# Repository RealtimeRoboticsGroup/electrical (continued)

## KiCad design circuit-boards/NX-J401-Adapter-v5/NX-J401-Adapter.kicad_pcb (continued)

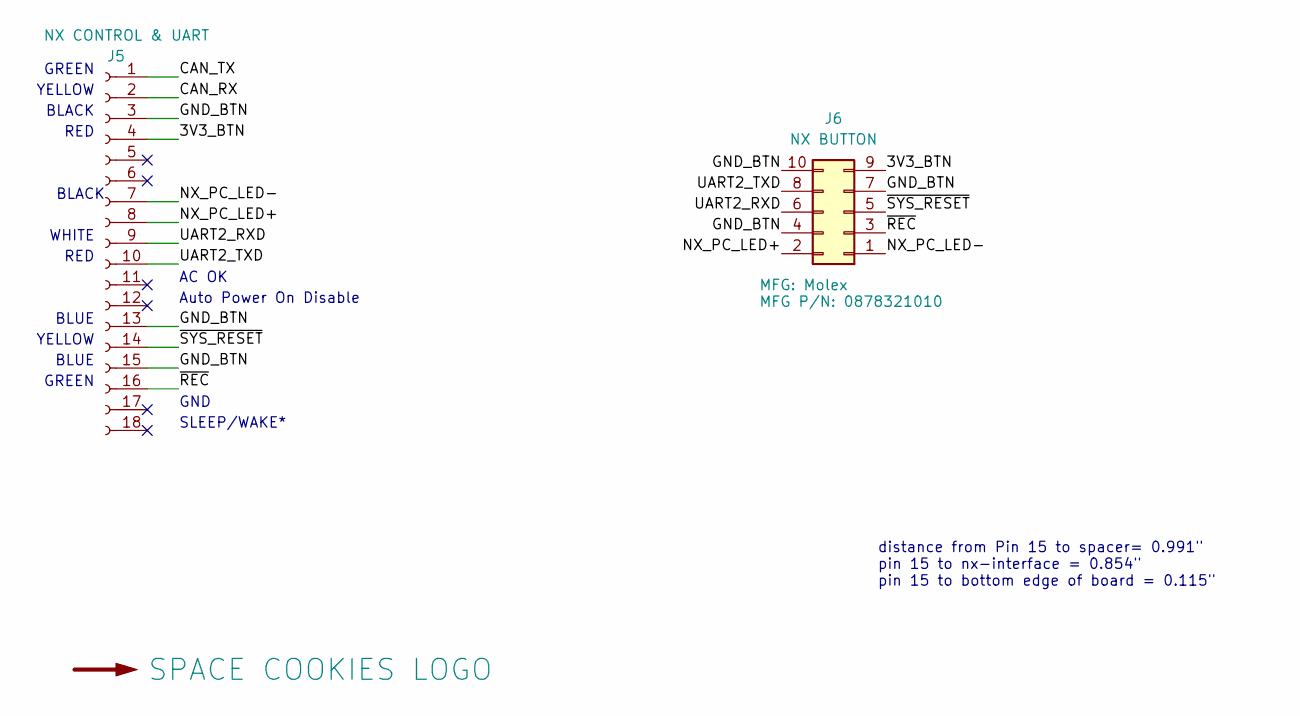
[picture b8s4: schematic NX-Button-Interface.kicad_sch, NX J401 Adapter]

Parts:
J5: NX CONTROL & UART; PinSocket_1x18_P2.54mm_Vertical; MFG P/N PPTC181LFBN-RC
J6: NX BUTTON; Molex-878321010; MFG P/N 0878321010
LOGO2: SPACE COOKIES LOGO; SPACE_COOKIES_LOGO_15mm

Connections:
/NX Button Interface/3V3_BTN: J5.4, J6.9
/NX Button Interface/CAN_RX: J5.2
/NX Button Interface/CAN_TX: J5.1
/NX Button Interface/GND_BTN: J5.3, J5.13, J5.15, J6.4, J6.7, J6.10
/NX Button Interface/NX_PC_LED+: J5.8, J6.2
/NX Button Interface/NX_PC_LED-: J5.7, J6.1
/NX Button Interface/UART2_RXD: J5.9, J6.6
/NX Button Interface/UART2_TXD: J5.10, J6.8
/NX Button Interface/~REC: J5.16, J6.3
/NX Button Interface/~SYS_RESET: J5.14, J6.5

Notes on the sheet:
BLACK
YELLOW
BLUE
RED
AC OK
GND
Auto Power On Disable
SLEEP/WAKE*
GREEN
distance from Pin 15 to spacer= 0.991" pin 15 to nx-interface = 0.854" pin 15 to bottom edge of board = 0.115"
WHITE

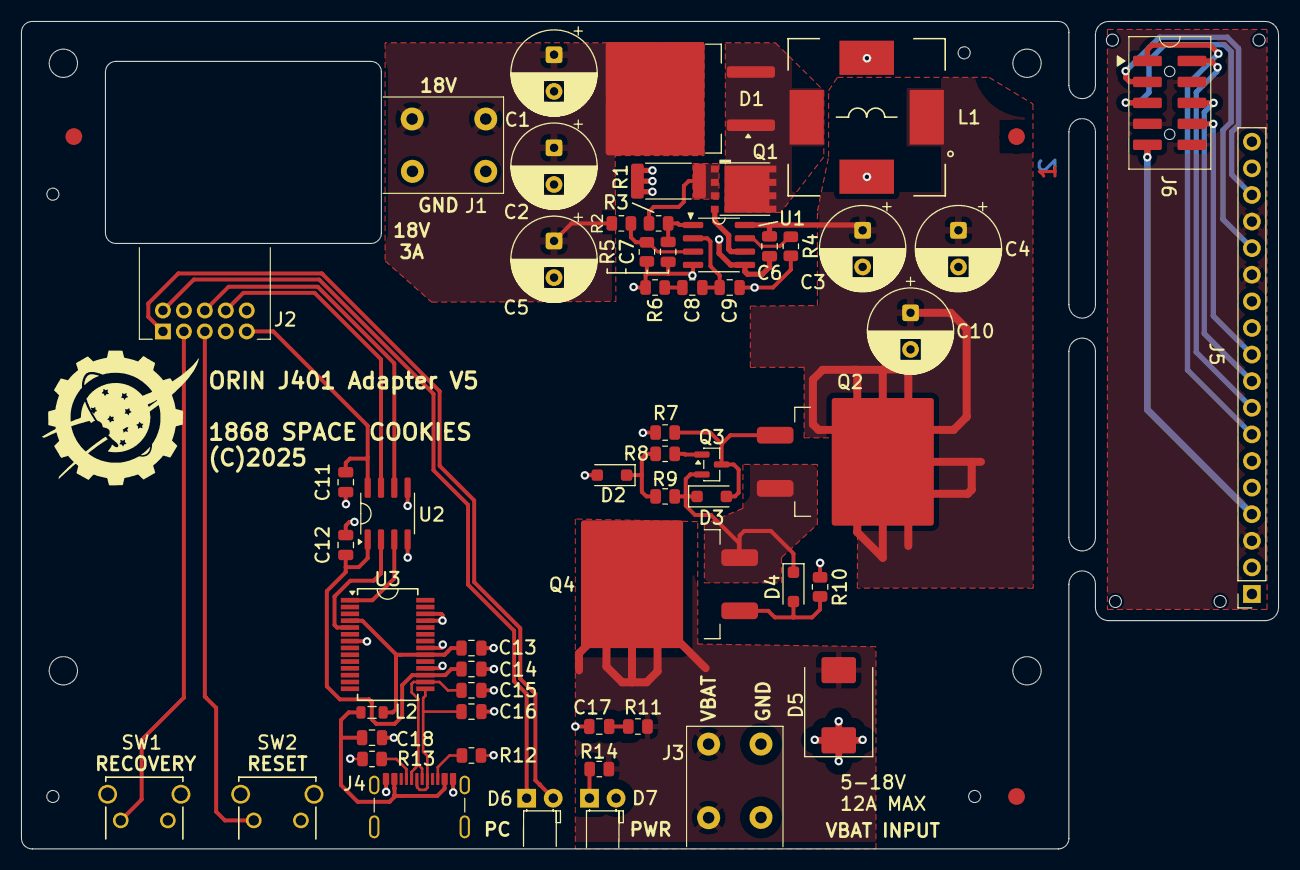
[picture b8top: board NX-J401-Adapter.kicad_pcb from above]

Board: 2 copper layers, 120.0 x 79.0 mm, 73 parts (1 on the bottom side), 45 nets.

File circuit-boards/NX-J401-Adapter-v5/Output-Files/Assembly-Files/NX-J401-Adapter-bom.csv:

"Item","QUANTITY","Reference","Value","MFG","MFG P/N","DIST","DIST P/N"
"1","1","C7","10pF-5%-50V-0805","Samsung Electro-Mechanics","CL21C100CBANNNC","Digikey","1276-2561-1-ND"
"2","1","C13","4.7uF-10%-25V-0805","Samsung Electro-Mechanics","CL21A475KAQNNNE","Digikey","1276-1244-1-ND"
"3","1","C17","4.7uF-10%-50V-0805","Murata Electronics","GRM21BR61H475KE51L","Digikey","490-10751-1-ND"
"4","3","C1,C2,C5","56uF 25V","Panasonic Electronic Components","25SEPF56M","Mouser","667-25SEPF56M "
"5","3","C11,C12,C14","0.1uF-10%-25V-0805","KEMET","C0805C104K3RACTU","Digikey","399-C0805C104K3RACTUCT-ND"
"6","2","C15,C16","47pF-5%-50V-0805","YAGEO","CC0805JRNPO9BN470","Digikey","311-1107-1-ND"
"7","3","C3,C4,C10","120uF 25V","Panasonic","25SEK120M","Digikey","P122635-ND"
"8","2","C6,C8","0.22uF-10%-50V-0805","KEMET","C0805C224K5RAC7800","Digikey","399-C0805C224K5RACTUCT-ND"
"9","2","C9,C18","0.01uF-10%-50V-0805","Samsung Electro-Mechanics","CL21B103KBANNNC","Digikey","1276-1015-1-ND"
"10","1","D1","STPS20M100SG-TR","STmicroelectronics","STPS20M100SG-TR","Digikey","497-10993-1-ND"
"11","1","D2","20V","Nexperia","BZT52H-C20,115","Digikey","1727-3596-1-ND"
"12","1","D5","24V","Littelfuse","SMDJ24CA","Digikey","SMDJ24CACT-ND"
"13","2","D3,D4","15V","Nexperia","BZT52H-C15,115","Digikey","1727-3593-1-ND"
"14","2","D6,D7","PC,PWR","Kingbright","WP937EGW","Digikey","754-1751-ND"
"15","1","J2","NX BUTTON","Molex","0878321010","Digikey","WM4227-ND"
"16","1","J4","USB_C_Receptacle_USB2.0_14P","Molex","2171790001","Digikey","900-2171790001CT-ND"
"17","2","J1,J3","Power,V_OUT","Weidmuller","1824740000","Digikey","281-2110-ND"
"18","1","L1","4.7 uH-8m-20%","Vishay Dale","IHLE5050FHER4R7M5A ","Mouser","70-IHLE5050FHR4R7M5A "
"19","1","L2","HZ0805E601R-10","Laird-Signal Integrity Products","HZ0805E601R-10","Digikey","240-2399-1-ND"
"20","1","Q1","CSD16322Q5","Texas Instruments","CSD16322Q5","Digikey","296-25112-1-ND"
"21","1","Q3","MMBT3906LT1G","onsemi","MMBT3906LT1G","Digikey","MMBT3906LT1GOSCT-ND"
"22","2","Q2,Q4","SQM40061EL_GE3","Vishay Siliconix","SQM40061EL_GE3","Digikey","SQM40061EL_GE3CT-ND"
"23","1","R1","4.0m-1%-2512","Bourns Inc.","CRE2512-FZ-R004E-3","Digikey","CRE2512-FZ-R004E-3CT-ND"
"24","1","R2","14.0k-1%-0805","Yageo","RC0805FR-0714KL","Digikey","311-14.0KCRCT-ND"
"25","1","R3","100R-1%-0805","Yageo","RC0805FR-07100RL","Digikey","311-100CRCT-ND"
"26","1","R4","59.0k-1%-0805","Yageo","RC0805FR-0759KL","Digikey","311-59.0KCRCT-ND"
"27","1","R11","1.00R-1%-0805","Vishay Dale","CRCW08051R00FKEAHP","Digikey","541-1.00TCT-ND"
"28","3","R5,R6,R9","1.05k-1%-0805","Yageo","RC0805FR-071K05L","Digikey","311-1.05KCRCT-ND"
"29","6","R7,R8,R10,R12-R14","5.10k-1%-0805","Yageo","RC0805FR-075K1L","Digikey","311-5.10KCRCT-ND"
"30","2","SW1,SW2","RECOVERY,RESET","E-Switch","TL1105VF100Q","Digikey","EG2507-ND"
"31","1","U1","LM3478MA","Texas Instruments","LM3478MAX/NOPB","Digikey","296-38111-1-ND"
"32","1","U2","ISO6721BDR","Texas Instruments","ISO6721BDR","Digikey","296-ISO6721BDRCT-ND"
"33","1","U3","FT232RNL","FTDI","FT232RNL","Digikey","768-FT232RNL-REELCT-ND"

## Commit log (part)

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2025-01-05 Initial commit from private repo
2025-01-14 Initial Checkin of NX J401 Adapter PCB
2025-01-14 Update NX J401 Adapter to add PC LED and swap buttons
2025-01-14 Add NX Button Interface Board
2025-01-16 Update NX-J401 and NX Button Interface boards
2025-01-16 Clarify schematic analog ground
2025-01-16 Minor fixes
2025-04-26 Add NX Indicator board. Change to one oscillator
2025-04-28 Initial checkin of WIP
2025-04-28 Changed to 1 encoder, all connectors to SMD right angle SL
2025-06-08 Add Pico CAN PCBA
2025-06-08 Minor update to PicoCAN. Add JLC assembly docs
2025-06-10 Checkin post review
2025-06-14 Changed oscillator back to ECS5032
2025-06-14 Missed schematic
2025-06-14 Update BOM
2025-06-25 Copy of https://github.com/Pier836/MCP2518FD-on-Raspberry-Pico to start picocan
2025-06-25 Set defs to match picoCAN board. Tweak code to compile
2025-09-17 Initial checkin of Button Interface and Adapter with USB-serial adapter addition
2025-09-20 Initial check in of Mini PDB V2
2025-09-20 Changed drawing sheet to Space Cookies
2025-09-20 Update using Space Cookies sheet template
2025-09-26 adjust header to match nx-adapter
2025-09-28 Add over voltage protection to NX adapter circuit. Also reduce component height
2025-10-07 Fix name on PCB
2025-10-19 Change NX-J401-Adapter to reduce the PCB standoff spacing.
2025-10-19 Update NX-ButtonInterface-v2 to be compatible with NX-J401-Adapter-v5
2025-10-19 Update step file of NX-J401-Adapter
2025-10-23 Update silk to new part number
2025-10-23 Update NX J401 to combine button interface and adapter. change header to right angle
2025-10-25 Fix bom to reduce line items. Addd zip tie slots. Add 1.5mm tooling holes
2025-11-09 Add ability to build pico2 binaries with bazel
2025-11-09 Add license
2025-11-12 Add bazel target for picocan and binary for it
2025-11-12 Fix usb printing
2025-11-25 Add ribbon cable connector and cable to schematic
2025-12-13 Adding ibom for J401 Adapter board
2025-12-18 Fixed IDC connector part number
2025-12-26 Initial check in
2025-12-26 Update footprints
2025-12-27 Pico Button Board initial placement
2025-12-28 Pico Button Board initial pcb checkin
2025-12-28 Update Pico Button Board Layout
2025-12-28 Updated Pico2 step file
2025-12-30 Changed button input circuit to use mux. Changed ADC3 to an external SPI ADC
2025-12-30 Minor schematic fix
2025-12-31 Add power over CAN to supply joystick from button interfaces.
2025-12-31 Change diodes to schottky. Change 5V setpoint to 5.18V
2025-12-31 DNP joystick pull down resistors
2026-01-01 Initial check in of roboRIO interface
2026-01-01 Update HTML bom to for DNPs
2026-01-02 Beam Break initial check in
2026-01-04 Minor schematic field update. Add jupyter notebook for power supply analysis
2026-01-05 Chagned opto-coupler to totem pole output to drive 5V DIO with weak pull-up
2026-01-05 Improved placement and routing
2026-01-06 Increased length to 2.2in
2026-01-21 Added power indicator to button board
2026-01-22 Lower impedance of battery override input
2026-01-25 initial checkin
2026-01-25 modify roborio bom to add sockets to bottom of board
2026-01-25 add bottom silk to gerbers
2026-01-25 Update power pour
2026-01-25 Changed Signal LED to Yellow
2026-02-09 Update RRIB bom to include applicable interfaces
2026-02-22 changed the roborio interface stuffing
2026-02-22 Update roborio interface assy
2026-02-22 Fix inductor mfg part number
2026-03-22 Updated repo license to Solderpad V2.1
2026-03-22 Update Apache License copyright
2026-03-22 Minor update of template to use COPYRIGHT_YEAR instead of YEAR
2026-03-23 Add open source license to mag encoder.
2026-05-18 Changed canable to use 3.3V power form USB to use key-e connector that breaks out USB and 3V3
2026-05-19 WIP update
2026-05-20 Changed USB header ot pico lock and light pipe to single row
2026-05-21 Added ideal diode circuit for reverse polarity and output or-ing
2026-05-22 Starting component placement
2026-05-22 rearrange power supply
2026-05-24 Improved placement. Pre-routing
2026-05-24 Initial fully routed PCB
2026-05-25 Initial complete routing
2026-05-26 Moved the Vout connector to increase clearance
2026-05-27 Add rails to M.2 adapter. Minor fixes to NX J401 adapter
2026-05-29 Prepare USB-m2 for manufacture
2026-06-15 Adjusted connector positioning to more closely match J401.
2026-06-20 Minor updates
